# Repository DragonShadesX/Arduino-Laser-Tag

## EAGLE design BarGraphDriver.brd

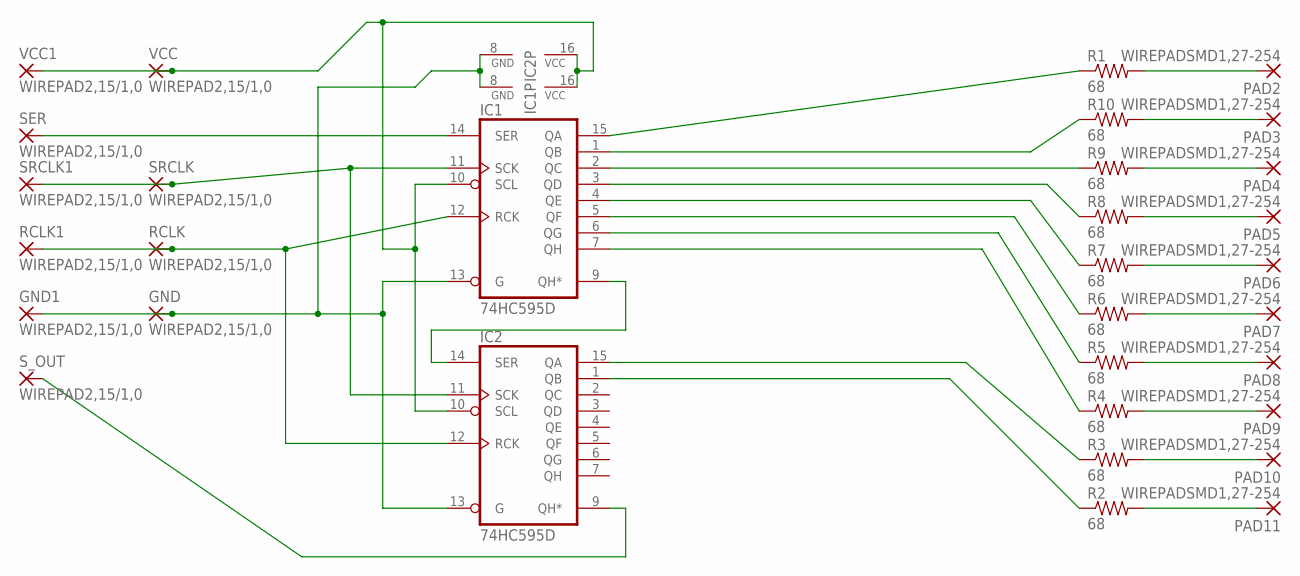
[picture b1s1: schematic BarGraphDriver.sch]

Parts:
GND, GND1: WIREPAD2,15/1,0; 2,15/1,0
IC1, IC2: 74HC595D; SO16
PAD2, PAD3, PAD4, PAD5, PAD6, PAD7, PAD8, PAD9, PAD10, PAD11: WIREPADSMD1,27-254; SMD1,27-2,54
R1, R2, R3, R4, R5, R6, R7, R8, R9, R10: 68; 1206
RCLK, RCLK1: WIREPAD2,15/1,0; 2,15/1,0
SER: WIREPAD2,15/1,0; 2,15/1,0
SRCLK, SRCLK1: WIREPAD2,15/1,0; 2,15/1,0
S_OUT: WIREPAD2,15/1,0; 2,15/1,0
VCC, VCC1: WIREPAD2,15/1,0; 2,15/1,0

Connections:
GND: GND.1, GND1.1, IC1.8 (GND), IC1.13 (G), IC2.8 (GND), IC2.13 (G)
unnamed: PAD11.1, R2.2
unnamed: PAD10.1, R3.2
unnamed: PAD9.1, R4.2
unnamed: PAD8.1, R5.2
unnamed: PAD7.1, R6.2
unnamed: PAD6.1, R7.2
unnamed: PAD5.1, R8.2
unnamed: PAD4.1, R9.2
unnamed: PAD3.1, R10.2
unnamed: PAD2.1, R1.2
unnamed: IC1.15 (QA), R1.1
unnamed: IC1.1 (QB), R10.1
unnamed: IC1.2 (QC), R9.1
unnamed: IC1.3 (QD), R8.1
unnamed: IC1.4 (QE), R7.1
unnamed: IC1.5 (QF), R6.1
unnamed: IC1.6 (QG), R5.1
unnamed: IC1.7 (QH), R4.1
unnamed: IC2.15 (QA), R3.1
unnamed: IC2.1 (QB), R2.1
unnamed: IC1.9 (QH*), IC2.14 (SER)
RCLK: IC1.12 (RCK), IC2.12 (RCK), RCLK.1, RCLK1.1
SER: IC1.14 (SER), SER.1
SRCLK: IC1.11 (SCK), IC2.11 (SCK), SRCLK.1, SRCLK1.1
S_OUT: IC2.9 (QH*), S_OUT.1
VCC: IC1.10 (SCL), IC1.16 (VCC), IC2.10 (SCL), IC2.16 (VCC), VCC.1, VCC1.1

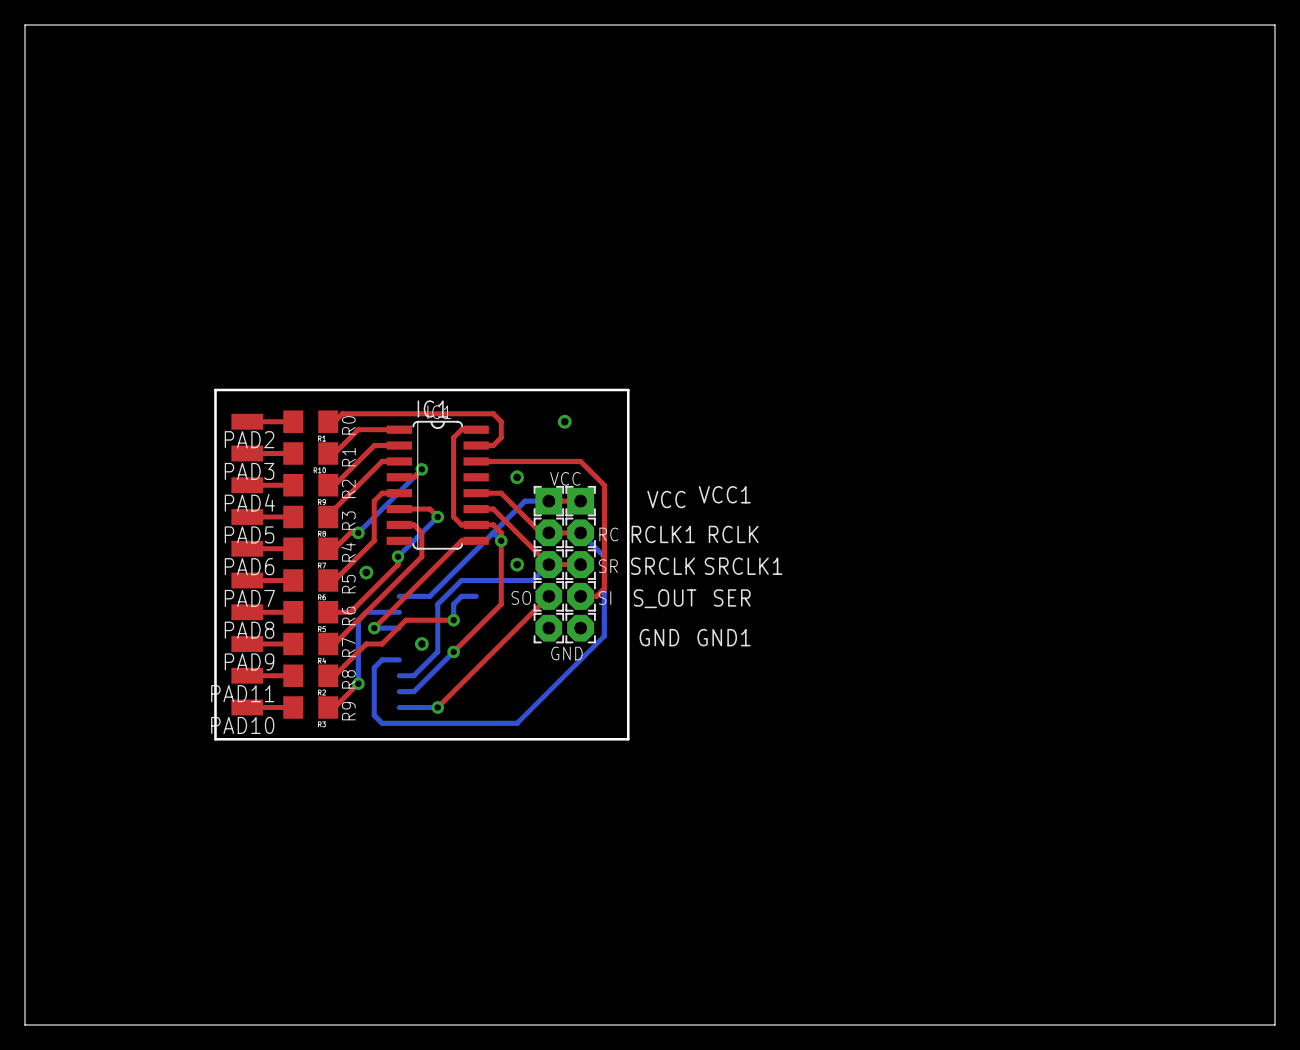
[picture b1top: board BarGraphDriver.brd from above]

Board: 2 copper layers, 100.0 x 80.0 mm, 32 parts (1 on the bottom side), 27 nets.

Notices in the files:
parts and their libraries:
SparkFun-Resistors: Licensing: Creative Commons ShareAlike 4.0 International - https://creativecommons.org/licenses/by-sa/4.0
